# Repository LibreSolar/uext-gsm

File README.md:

# GSM board based on SIM800L for UEXT connector

## Features

- Separate power supply from 12V or 5V (GSM board needs 4.2V and 2A)
- Reverse polarity protection for separate power supply
- UEXT connector to communicate with host MCU

### Top side 

### Bottom side

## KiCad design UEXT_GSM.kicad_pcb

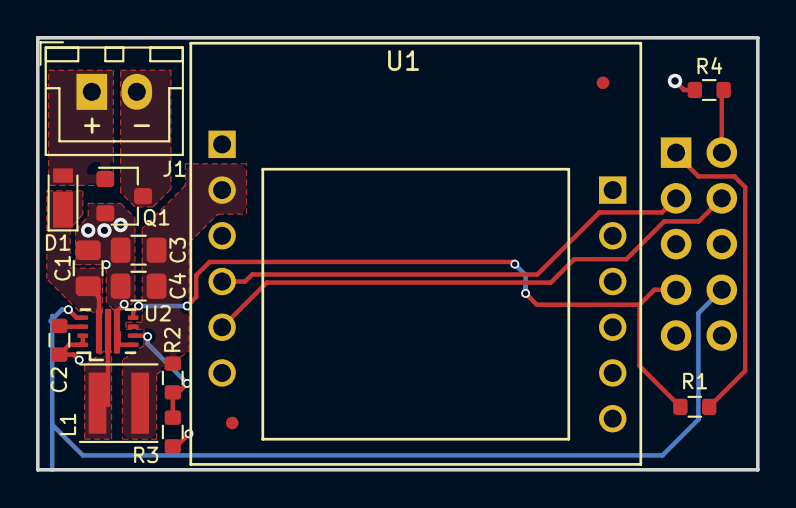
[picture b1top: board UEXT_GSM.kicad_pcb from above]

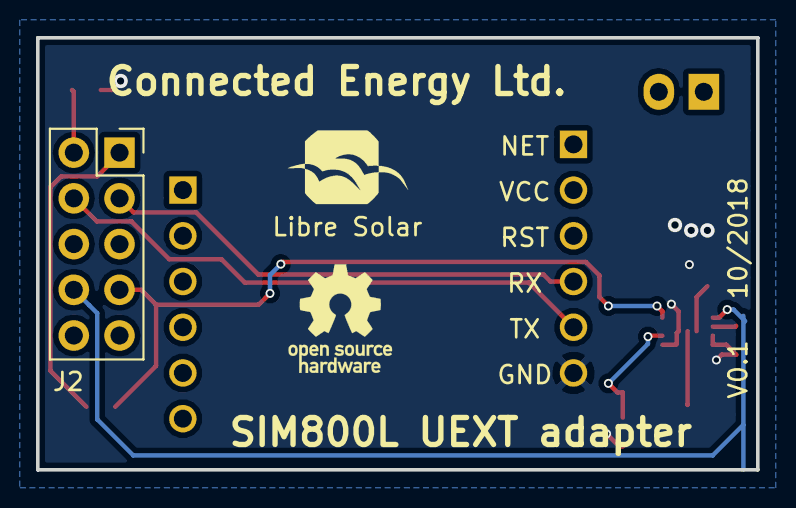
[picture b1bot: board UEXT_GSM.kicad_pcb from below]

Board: 2 copper layers, 40.0 x 24.0 mm, 16 parts (2 on the bottom side), 14 nets.

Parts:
C1: 10uF; C_0805_2012
C2: 2.2n; C_0603_1608
C3, C4: 22uF; C_0805_2012
D1: RSX051VAM30TR; D_TUMD2
J1: Conn_01x02_Male; JST_XH_B02B-XH-A_1x02_P2.50mm_Vertical
J2: UEXT; PinSocket_2x05_P2.54mm_Vertical
L1: 2.2uH; L_Coilcraft_XxL4020
LOGO1: LibreSolar_Logo; LIBRESOLAR_LOGO
Q1: DMN3023L-7; SOT-23
R1, R3: 100k; R_0603_1608
R2: 499k; R_0603_1608
R4: 0R; R_0603_1608
U1: SIM800L; Sim800L
U2: TPS62147; VQFN_RGX0011A

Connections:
+3V3: J2.1, R1.2
/EN: J2.8, U2.8
/PG: J2.7, R1.1, U2.7
/UEXT_RX: J2.4, U1.5
/UEXT_TX: J2.3, U1.4
GND: C1.2, C2.2, C3.2, C4.2, Q1.2, R3.2, R4.2, U1.6, U2.3, U2.4, U2.10, U2.11
unnamed: C2.1, U2.9
unnamed: D1.2, J1.1, Q1.1
unnamed: J1.2, Q1.3
unnamed: J2.2, R4.1
unnamed: L1.1, U2.2
unnamed: R2.2, R3.1, U2.5
VBAT: C1.1, D1.1, U2.1
VCC: C3.1, C4.1, L1.2, R2.1, U1.2, U2.6

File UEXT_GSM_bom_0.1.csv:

Component,Description,Part,References,Value,Footprint,Quantity Per PCB,Datasheet,Remarks,PartNumber,Manufacturer,DNP
1,Unpolarized capacitor,C,C1,10uF,C_0805_2012,1,,Alternative: TDK C2012X5R1E106K085AC,GRM21BC71E106KE11L,Murata,
2,Unpolarized capacitor,C,C2,2.2n,C_0603_1608,1,,"minimum 10V, X5R",885012206085,Würth,
3,Unpolarized capacitor,C,C3 C4,22uF,C_0805_2012,2,,"minimum 10V, X5R",LMK212BBJ226MG-T,Tayo Yuden,
4,Diode Schottky,D_Schottky,D1,RSX051VAM30TR,D_TUMD2,1,,,RSX051VAM30TR,ROHM,
5,"Generic connector, single row, 01x02, script generated (kicad-library-utils/schlib/autogen/connector/)",Conn_01x02_Male,J1,Conn_01x02_Male,JST_XH_B02B-XH-A_1x02_P2.50mm_Vertical,1,~,,,,X
6,,UEXT,J2,UEXT,PinSocket_2x05_P2.54mm_Vertical,1,http://wppro.com/content/de/produkte/buchsenleisten/raster-2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,,157B-05-2-00,W+P,
7,Inductor,L,L1,2.2uH,L_Coilcraft_XxL4020,1,,,XFL4020-222,Coilcraft,
8,,LibreSolar_Logo,LOGO1,LibreSolar_Logo,LIBRESOLAR_LOGO,1,,,,,X
9,Transistor N-MOSFETwith substrate diode (general),Q_NMOS_GSD,Q1,DMN3023L-7,SOT-23,1,,,DMN3023L-7,Diodes Incorporated,
10,Resistor,R,R4,0R,R_0603_1608,1,,,,,X
11,Resistor,R,R1 R3,100k,R_0603_1608,2,,,RC0603FR-07100KL,Yageo,
12,Resistor,R,R2,499k,R_0603_1608,1,,,RC0603FR-07499KL,Yageo,
13,,SIM800L,U1,SIM800L,Sim800L,1,,,,,
14,"3A Step-Down Converter with DCS-Control, Adjustable Output Voltage, 3-17V Input Voltage, QFN-16",TPS62147,U2,TPS62147,VQFN_RGX0011A,1,http://www.ti.com/lit/ds/symlink/tps62130.pdf,,TPS62147RGXR,Texas Instruments,





Component Groups:,14
Component Count:,16
Fitted Components:,16
Number of PCBs:,1
Total components:,16
Schematic Version:,0.1
Schematic Date:,2018-10-24
BoM Date:,Do 25 Okt 2018 14:22:35 CEST
Schematic Source:,/home/martin/LibreSolar/2_Development/04_Hardware/UEXT_GSM/UEXT_GSM.sch
KiCad Version:,Eeschema 5.0.0
